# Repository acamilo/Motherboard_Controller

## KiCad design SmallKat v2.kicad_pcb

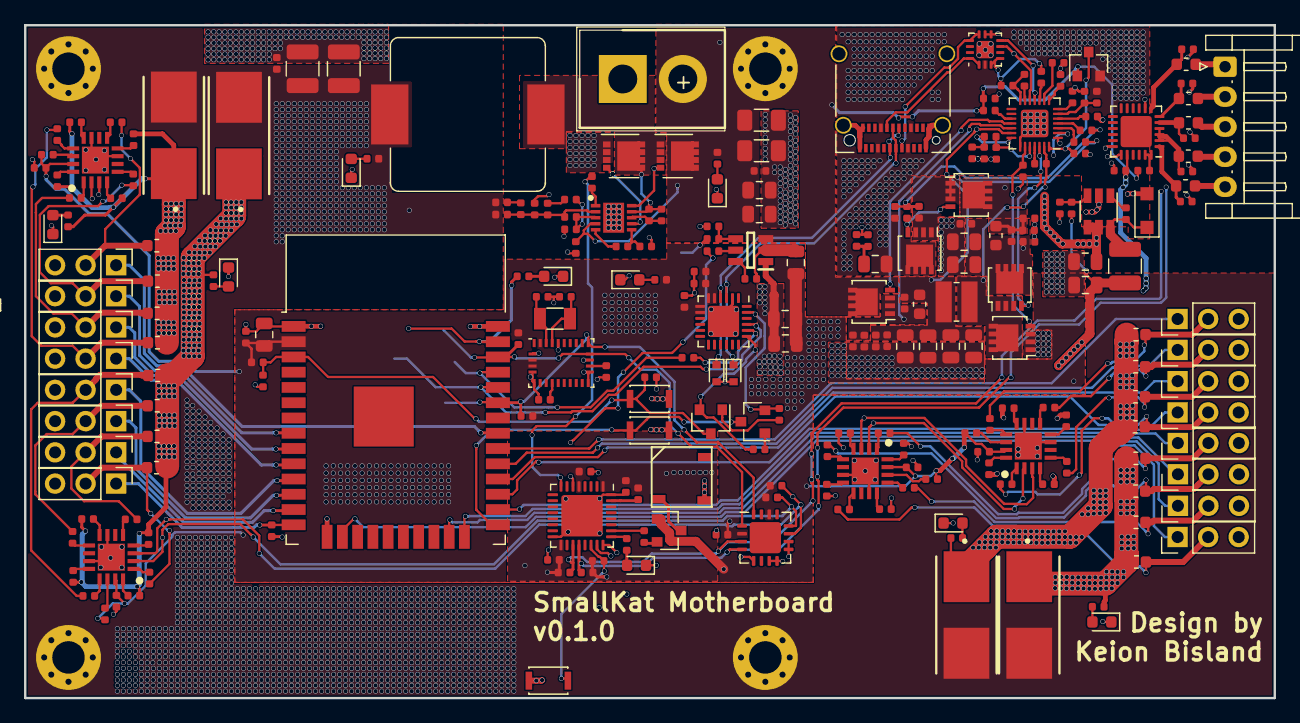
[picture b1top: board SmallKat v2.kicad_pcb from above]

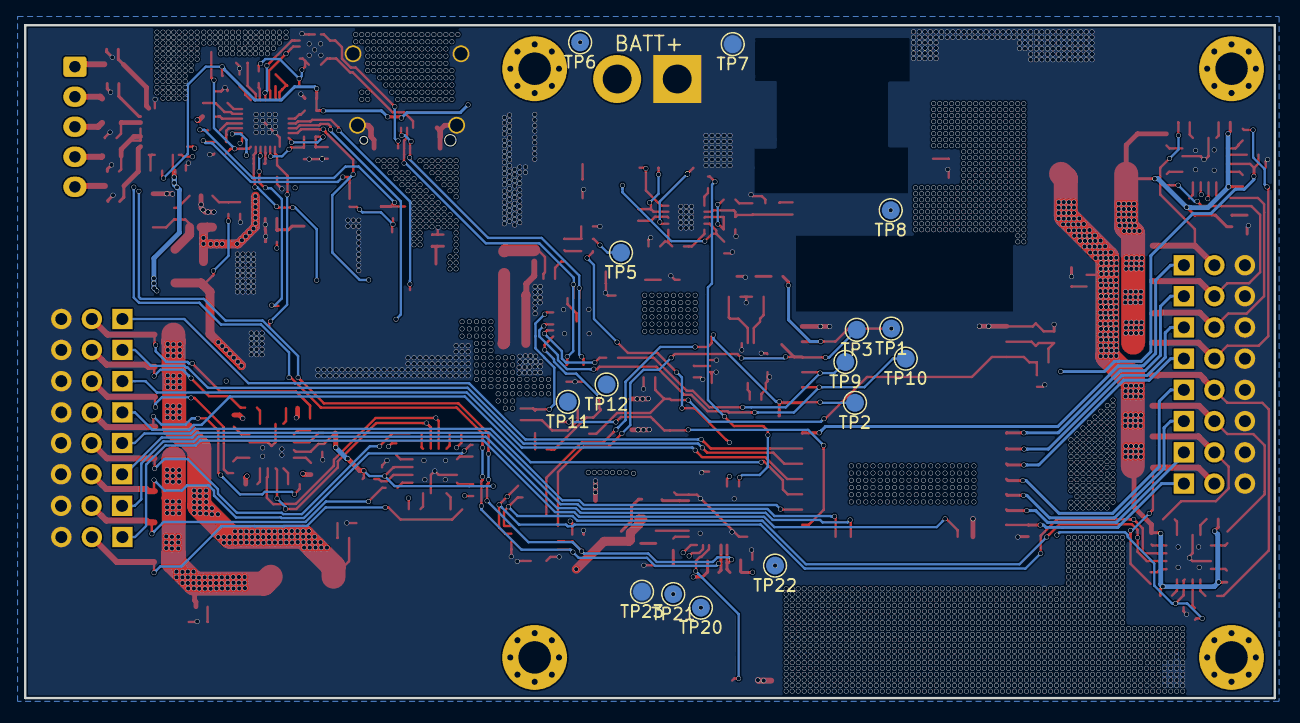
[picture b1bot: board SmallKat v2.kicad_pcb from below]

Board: 4 copper layers, 104.0 x 56.0 mm, 272 parts (15 on the bottom side), 177 nets.

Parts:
BZ1: Buzzer; KLJ-5030
C1, C2, C35, C63, C66: 10uF; C_0805_2012Metric
C3, C5, C24, C72, C75, C76, C77: 22uF; C_0805_2012Metric
C4, C6, C7, C17, C20, C25, C26, C28, C29, C31, C32, C37, C45, C46, C49, C51, C52, C53, C54, C55, C57, C59, C64, C70, C71, C73, C78, C79, C80: 0.1uF; C_0402_1005Metric
C8, C9: 10pF; C_0402_1005Metric
C10: 1000pF; C_0402_1005Metric
C11, C56, C58: 100pF; C_0402_1005Metric
C12: 10nF; C_0402_1005Metric
C13, C22, C50, C60, C61, C65, C81, C82: 1uF; C_0402_1005Metric
C14, C27: 4.7uF; C_0402_1005Metric
C15: 470nF; C_0402_1005Metric
C16, C18: 10uF; C_1206_3216Metric
C19, C21: 100uF; C_1210_3225Metric
C23, C47: 2.2uF; C_0805_2012Metric
C48: 2200pF; C_0402_1005Metric
C62: 0.01uF; C_0402_1005Metric
C67: 470pF; C_0402_1005Metric
C68: 0.047uF; C_0402_1005Metric
C69, C74: 10uF; C_0402_1005Metric
D1, D2, D3, D4, D18, D23, D24, D25, D26: LED; LED_0603_1608Metric
D5: BAT54C; SOT-23
D7, D8: D_TVS; D_SOD-523
D17: MA2YD26; D_SOD-123F
F1, F2, F3, F4: Fuse; 0154.250DR
H1, H2, H3, H4: MountingHole_Pad; MountingHole_2.7mm_M2.5_Pad_Via
IC1: TPS562201DDCR; SOT95P280X110-6N
IC2: TPS40192DRCT; SON50P300X300X100-11N
IC4, IC5, IC6, IC7: MAX34409ETE+; QFN65P400X400X80-17N
J1, J2, J3, J4, J5, J6, J7, J8, J10, J11, J12, J13, J14, J15, J16, J17: Conn_01x03_Male; PinHeader_1x03_P2.54mm_Vertical
J9: Conn_01x02_Male; SHDR2W320P716_1X2_1574X813X1588P
J19: USB_C_Receptacle; USB_C_Receptacle_Amphenol_12401610E4-2A_CircularHoles
J21: Conn_01x05_Male; JST_EH_S5B-EH_1x05_P2.50mm_Horizontal
L1: 4.7uH; L_0805_2012Metric
L2: 1uH; L_Bourns_SRP1245A
L3: 15uH; L_1210_3225Metric
L4: L; L_Wuerth_MAPI-3020
Q1, Q2: BUK9M120-100EX; VSON-8_3.3x3.3mm_P0.65mm_NexFET
Q3, Q4: MMBT3904; SOT-23
Q7: 2N3905; SOT-23
Q8, Q9: BUK9M120-100EX; LFPAK33
Q10, Q11: CSD17307Q5A; LFPAK33
Q12: Si7141DP; LFPAK33
R1, R7, R44: 330R; R_0402_1005Metric
R2: 1K; R_0402_1005Metric
R3: 3.4K; R_0402_1005Metric
R4, R5, R8, R10, R11, R21, R25, R26, R27, R43, R45, R46, R47, R48, R56, R117, R119, R125, R126, R127: 10K; R_0402_1005Metric
R6: 120K; R_0402_1005Metric
R9: 33.2K; R_0402_1005Metric
R12: 2.18k; R_0402_1005Metric
R13: 20k; R_0402_1005Metric
R14: 2.61k; R_0402_1005Metric
R15: 4.22k; R_0402_1005Metric
R16: 3.9k; R_0402_1005Metric
R17, R18, R19: 100k; R_0402_1005Metric
R20, R63, R73, R78, R86: 20K; R_0402_1005Metric
R22, R23, R37, R38, R124: 47R; R_0603_1608Metric
R24: 470R; R_0402_1005Metric
R49, R52: 3.9K; R_0402_1005Metric
R50: 430K; R_0402_1005Metric
R51: 66.5K; R_0402_1005Metric
R53: 4.7R; R_0402_1005Metric
R54, R55: 4.02K; R_0402_1005Metric
R57, R61, R62, R69, R70, R74, R75, R79, R80, R87, R88, R91, R92, R99, R100, R104, R105, R123: 0.01R; R_0603_1608Metric
R58: 30.1K; R_0402_1005Metric
R59, R60, R64, R65, R67, R68, R71, R72, R76, R77, R81, R82, R84, R85, R89, R90, R93, R94, R95, R96, R98, R101, R102, R103, R106, R107, R108, R109, R111, R112, R113, R114: 100R; R_0402_1005Metric
R66, R83, R97, R110: 0R; R_0402_1005Metric
R118: 3M; R_0402_1005Metric
R120: 316K; R_0402_1005Metric
R121: 100K; R_0402_1005Metric
R122: 10R; R_0402_1005Metric
SW1, SW2, SW5: SW_SPST; SW_SPST_CK_KXT3
TP1, TP2, TP3, TP5, TP6, TP7, TP8, TP9, TP10, TP11, TP12, TP20, TP21, TP22, TP23: TestPoint; TestPoint_Pad_D1.5mm
U1: BNO055; LGA-28_5.2x3.8mm_P0.5mm
U2: LM2840Y; TSOT-23-6
U3: ESP32-WROOM-32
U4: CP2102N-A01-GQFN24; QFN-24-1EP_4x4mm_P0.5mm_EP2.6x2.6mm
U6: STM32L432KBUx; QFN-32-1EP_5x5mm_P0.5mm_EP3.45x3.45mm
U11: FUSB302BMPX; WQFN-14-1EP_2.5x2.5mm_P0.5mm_EP1.45x1.45mm
U12: BQ24770; QFN-28-1EP_4x4mm_P0.4mm_EP2.3x2.3mm
U13: bq76925; QFN-24-1EP_4x4mm_P0.5mm_EP2.6x2.6mm
U14: PCA9641; UQFN-16-1EP_4x4mm_P0.65mm_EP2.6x2.6mm
Y1: 32.768kHz; Crystal_SMD_3215-2Pin_3.2x1.5mm

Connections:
+3.3VA: C35.1, C37.1, C45.1, C46.1, L3.2, R3.1, R43.2, R45.1, R46.1, R48.1, TP22.1, U6.1, U6.5, U6.17
+3V3: C3.1, C5.1, C24.1, C26.1, C27.1, C28.1, C29.2, C52.1, C53.1, C54.1, C55.1, C81.1, C82.1, IC4.15, IC5.15, IC6.15, IC7.15, L1.1, Q7.1, R4.2, R5.2, R7.1, R9.1, R27.1, R56.2, R66.1, R83.1, R97.1, R110.1, R117.2, R119.1, R126.1, R127.1, TP5.1, U1.3, U1.4, U1.28, U3.2, U4.5, U4.6, U4.7, U4.8, U11.3, U11.4, U13.20, U14.2, U14.14
+6V: C10.1, C19.1, C21.1, C22.1, F1.2, F2.2, F3.2, F4.2, H1.1, H2.1, H4.1, L2.2, R13.1, R20.1, TP8.1
+BATT: C1.2, C2.2, C4.2, C13.1, C16.1, C18.1, C64.1, D5.1, H3.1, IC1.3, IC2.4, J9.2, Q1.5, Q12.5, R6.1, R122.1, R125.2, TP6.1
/MainBoard/3.3VEN: R10.1, U6.6
/MainBoard/6VEN: R17.1, U6.8
/MainBoard/BatteryBalancer/C0: J21.1, R124.2
/MainBoard/BatteryBalancer/C1: J21.2, R38.2
/MainBoard/BatteryBalancer/C2: J21.3, R37.2
/MainBoard/BatteryBalancer/C3: J21.4, R23.2
/MainBoard/BatteryBalancer/C4: J21.5, R22.2
/MainBoard/CC1: J19.A5, U11.10, U11.11
/MainBoard/CC2: J19.B5, U11.1, U11.14
/MainBoard/ESP32Module/DTR: Q4.2, R25.2, TP11.1, U4.23
/MainBoard/ESP32Module/EN: C31.1, C32.1, Q3.3, R27.2, SW2.2, U3.3
/MainBoard/ESP32Module/IO0: Q4.3, SW1.2, U3.25
/MainBoard/ESP32Module/IO23: R1.1, TP1.1, U3.37
/MainBoard/ESP32Module/RTS: Q3.2, R26.2, TP12.1, U4.19
/MainBoard/ESP32Module/RXD: TP10.1, U3.34, U4.21
/MainBoard/ESP32Module/TXD: R24.1, TP9.1, U3.35
/MainBoard/ESP32Module/USBD_N: D7.1, J19.A7, J19.B7, U4.4
/MainBoard/ESP32Module/USBD_P: D8.1, J19.A6, J19.B6, U4.3
/MainBoard/SAFETYSCL: R45.2, U6.19, U11.6, U12.12, U13.19, U14.3
/MainBoard/SAFETYSDA: R46.2, U6.20, U11.7, U12.11, U13.18, U14.4
/MainBoard/SCL: R4.1, TP3.1, U1.19, U3.36, U14.1
/MainBoard/SDA: R5.1, TP2.1, U1.20, U3.33, U14.16
/MainBoard/SERVO0: J1.1, R21.1, U3.14
/MainBoard/SERVO1: J3.1, U3.13
/MainBoard/SERVO2: J5.1, U3.12
/MainBoard/SERVO3: J7.1, U3.11
/MainBoard/SERVO4: J10.1, U3.10
/MainBoard/SERVO5: J12.1, U3.9
/MainBoard/SERVO6: J14.1, U3.8
/MainBoard/SERVO7: J16.1, U3.31
/MainBoard/SERVO8: J2.1, U3.16
/MainBoard/SERVO9: J4.1, U3.23
/MainBoard/SERVO10: J6.1, U3.24
/MainBoard/SERVO11: J8.1, U3.26
/MainBoard/SERVO12: J11.1, U3.27
/MainBoard/SERVO13: J13.1, U3.28
/MainBoard/SERVO14: J15.1, U3.29
/MainBoard/SERVO15: J17.1, U3.30
/MainBoard/SafetyMCU/BUZZER: R47.2, U6.26
/MainBoard/SafetyMCU/MONITORING: R44.1, U6.25
/MainBoard/SafetyMCU/SOFTPOWER: R48.2, SW5.2, U6.22
/MainBoard/Servos/6V1: F1.1, R60.2, R61.2, R63.1, R65.2, R67.2, R69.2, R71.2, R74.2, R79.2
/MainBoard/Servos/6V2: F2.1, R73.1, R77.2, R82.2, R84.2, R87.2, R89.2, R91.2, R99.2, R104.2
/MainBoard/Servos/6V3: F3.1, R62.2, R70.2, R75.2, R78.1, R80.2, R94.2, R96.2, R98.2, R102.2
/MainBoard/Servos/6V4: F4.1, R86.1, R88.2, R92.2, R100.2, R105.2, R107.2, R109.2, R111.2, R113.2
/MainBoard/Servos/S1: J1.2, R59.2, R61.1
/MainBoard/Servos/S2: J3.2, R64.2, R69.1
/MainBoard/Servos/S3: J5.2, R72.2, R74.1
/MainBoard/Servos/S4: J7.2, R68.2, R79.1
/MainBoard/Servos/S5: J10.2, R85.2, R87.1
/MainBoard/Servos/S6: J12.2, R76.2, R91.1
/MainBoard/Servos/S7: J14.2, R81.2, R99.1
/MainBoard/Servos/S8: J16.2, R90.2, R104.1
/MainBoard/Servos/S9: J2.2, R62.1, R103.2
/MainBoard/Servos/S10: J4.2, R70.1, R101.2
/MainBoard/Servos/S11: J6.2, R75.1, R95.2
/MainBoard/Servos/S12: J8.2, R80.1, R93.2
/MainBoard/Servos/S13: J11.2, R88.1, R106.2
/MainBoard/Servos/S14: J13.2, R92.1, R108.2
/MainBoard/Servos/S15: J15.2, R100.1, R114.2
/MainBoard/Servos/S16: J17.2, R105.1, R112.2
/MainBoard/Sheet5DD4BDB8/ACDET: R50.2, R51.1, U12.6
/MainBoard/Sheet5DD4BDB8/ACDRV: R54.2, U12.4
/MainBoard/Sheet5DD4BDB8/BATDRV: Q12.4, U12.18
/MainBoard/Sheet5DD4BDB8/BTST: C68.2, U12.25
/MainBoard/Sheet5DD4BDB8/CMSRC: R55.2, U12.3
/MainBoard/Sheet5DD4BDB8/HIDRV: Q10.4, U12.26
/MainBoard/Sheet5DD4BDB8/LODRV: C67.1, Q11.4, U12.23
/MainBoard/Sheet5DD4BDB8/PHASE: C68.1, L4.1, Q10.1, Q10.2, Q10.3, Q11.5, U12.27
/MainBoard/Sheet5DD4BDB8/REGN: C65.1, R120.1, U12.24
/MainBoard/Sheet5DD4BDB8/SRN: C71.1, C73.2, C74.1, Q12.1, Q12.2, Q12.3, R123.1, U12.19
/MainBoard/Sheet5DD4BDB8/SRP: C69.1, C70.2, C71.2, C72.1, C75.1, C76.1, C77.1, L4.2, R123.2, U12.20
/MainBoard/Sheet5DD4BDB8/VCC28: C60.2, D5.3, U12.28
/MainBoard/_SCL: IC4.3, IC5.3, IC6.3, IC7.3, R127.2, U14.11
/MainBoard/_SDA: IC4.2, IC5.2, IC6.2, IC7.2, R126.2, U14.12
GND: BZ1.2, C1.1, C2.1, C3.2, C4.1, C5.2, C7.1, C8.1, C9.1, C13.2, C14.2, C16.2, C17.2, C18.2, C19.2, C20.2, C21.2, C22.2, C23.2, C24.2, C26.2, C27.2, C28.2, C29.1, C31.2, C32.2, C35.2, C37.2, C45.2, C46.2, C50.1, C51.1, C52.2, C53.2, C54.2, C55.2, C56.2, C58.2, C59.1, C60.1, C61.2, C62.1, C63.2, C64.2, C65.2, C66.2, C67.2, C69.2, C70.1, C72.2, C73.1, C74.2, C75.2, C76.2, C77.2, C78.2, C79.2, C80.2, C81.2, C82.2, D1.1, D2.1, D3.1, D4.1, D7.2, D8.2, D17.2, D18.1, D23.1, D24.1, D25.1, D26.1, IC1.1, IC2.11, IC4.7, IC4.11, IC4.17, IC5.7, IC5.11, IC5.17, IC6.7, IC6.11, IC6.17, IC7.7, IC7.11, IC7.17, J1.3, J2.3, J3.3, J4.3, J5.3, J6.3, J7.3, J8.3, J9.1, J10.3, J11.3, J12.3, J13.3, J14.3, J15.3, J16.3, J17.3, J19.A1, J19.A12, J19.B1, J19.B12, J19.S1, Q2.1, Q2.2, Q2.3, Q11.1, Q11.2, Q11.3, R2.2, R8.1, R11.2, R12.2, R16.2, R21.2, R49.2, R51.2, R52.2, R58.2, R121.1, SW1.1, SW2.1, SW5.1, TP7.1, TP23.1, U1.2, U1.5, U1.6, U1.15, U1.16, U1.18, U1.25, U2.2, U3.1, U3.15, U3.38, U3.39, U4.2, U4.25, U6.16, U6.32, U6.33, U11.8, U11.9, U11.15, U12.22, U12.29, U13.8, U14.5, U14.7, U14.8, U14.9, U14.10
unnamed: BZ1.1, Q7.3
unnamed: C6.1, IC1.6
unnamed: C6.2, IC1.2, L1.2
unnamed: C7.2, U1.9
unnamed: C8.2, U1.26, Y1.1
unnamed: C9.2, U1.27, Y1.2
unnamed: C10.2, R14.2
unnamed: C11.1, C12.1, IC2.3, R16.1
unnamed: C11.2, IC2.2, R12.1, R13.2, R14.1, R15.2
unnamed: C12.2, R15.1
unnamed: C14.1, IC2.6, R18.1
unnamed: C15.1, IC2.9, L2.1, Q1.1, Q1.2, Q1.3, Q2.5, R19.1
unnamed: C15.2, IC2.8, R19.2
unnamed: C17.1, R22.1, U13.1
unnamed: C20.1, R23.1, U13.2, U13.3, U13.4
unnamed: C25.1, D17.1, L3.1, U2.6
unnamed: C25.2, U2.1
unnamed: C47.2, R49.1, R52.1
unnamed: C48.2, C49.2, R53.2, R54.1
unnamed: C49.1, Q8.1, Q8.2, Q8.3, Q9.1, Q9.2, Q9.3, R55.1
unnamed: C50.2, C51.2, C57.2, Q9.5, R57.2, U12.2
unnamed: C56.1, U12.7
unnamed: C57.1, C59.2, C61.1, C63.1, C66.1, Q10.5, R57.1, U12.1
unnamed: C58.1, U12.8
unnamed: C62.2, R120.2, R121.2, U12.21
unnamed: C78.1, R37.1, U13.5
unnamed: C79.1, R38.1, U13.6
unnamed: C80.1, R124.1, U13.7
unnamed: D1.2, R1.2
unnamed: D2.2, R6.2
unnamed: D3.2, R7.2
unnamed: D4.2, R20.2
unnamed: D18.2, R44.2
unnamed: D23.2, R63.2
unnamed: D24.2, R73.2
unnamed: D25.2, R78.2
unnamed: D26.2, R86.2
unnamed: IC1.4, R8.2, R9.2
unnamed: IC1.5, R10.2
unnamed: IC2.1, R17.2
unnamed: IC2.5, R18.2
unnamed: IC2.7, Q2.4
unnamed: IC2.10, Q1.4
unnamed: IC4.1, R59.1
unnamed: IC4.4, R60.1
unnamed: IC4.5, R64.1
unnamed: IC4.8, R67.1
unnamed: IC4.9, R72.1
unnamed: IC4.12, R71.1
unnamed: IC4.13, R68.1
unnamed: IC4.14, R66.2
unnamed: IC4.16, R65.1
unnamed: IC5.1, R76.1
unnamed: IC5.4, R77.1
unnamed: IC5.5, R81.1
unnamed: IC5.8, R84.1
unnamed: IC5.9, R90.1
unnamed: IC5.12, R89.1
unnamed: IC5.13, R85.1
unnamed: IC5.14, R83.2
unnamed: IC5.16, R82.1
unnamed: IC6.1, R93.1
unnamed: IC6.4, R94.1
unnamed: IC6.5, R95.1
unnamed: IC6.8, R98.1
unnamed: IC6.9, R103.1
unnamed: IC6.12, R102.1
unnamed: IC6.13, R101.1
unnamed: IC6.14, R97.2
unnamed: IC6.16, R96.1
unnamed: IC7.1, R106.1
unnamed: IC7.4, R107.1
unnamed: IC7.5, R108.1
unnamed: IC7.8, R111.1
unnamed: IC7.9, R114.1
unnamed: IC7.12, R113.1
unnamed: IC7.13, R112.1
unnamed: IC7.14, R110.2
unnamed: IC7.16, R109.1
unnamed: Q3.1, R25.1
unnamed: Q4.1, R26.1
unnamed: Q7.2, R47.1
unnamed: Q8.4, Q9.4, R53.1
unnamed: R2.1, R3.2, U2.3
unnamed: R11.1, U1.17
unnamed: R24.2, U4.20
unnamed: R43.1, U6.31
unnamed: R56.1, U12.5
unnamed: R58.1, U12.9
unnamed: R117.1, U12.10
unnamed: R118.1, U12.13
unnamed: R118.2, R119.2, U12.14
unnamed: R122.2, U12.17
unnamed: R125.1, U13.23, U13.24
unnamed: TP20.1, U6.23
unnamed: TP21.1, U6.24
VBUS: C23.1, C47.1, C48.1, D5.2, J19.A4, J19.A9, J19.B4, J19.B9, Q8.5, R50.1, U2.4, U2.5, U11.2

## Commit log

2020-02-04 added version to silk
